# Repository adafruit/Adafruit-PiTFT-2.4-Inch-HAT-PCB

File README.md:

## Adafruit PiTFT 2.4 Inch HAT PCB

<a href="http://www.adafruit.com/products/2455"><br/>
Click here to purchase one from the Adafruit shop</a>

PCB files for the Adafruit PiTFT 2.4 Inch HAT. Format is EagleCAD schematic and board layout
* https://www.adafruit.com/product/2455

### DESCRIPTION
Is this not the cutest little display for the Raspberry Pi? It features a 2.4" display with 320x240 16-bit color pixels and a resistive touch overlay. The HAT uses the high speed SPI interface on the Pi and can use the mini display as a console, X window port, displaying images or video etc. Best of all it plugs right in on top!

It's designed to fit nicely onto the Pi Model Zero, A+, B+, Pi 2, Pi 3 - any Pi with a 2x20 connector.

This design uses the hardware SPI pins (SCK, MOSI, MISO, CE0, CE1) as well as GPIO #25 and #24. All other GPIO are unused. Since we had a tiny bit of space, there's 5 spots for optional slim tactile switches wired to five GPIOs, that you can use if you want to make a basic user interface. For example, you can use one as a power on/off button.

We have a right-angle 26-pin connector off to the side. You can connect a classic 26-pin Raspberry Pi GPIO cable in order to access the rest of the GPIO through a Cobbler, etc.

To make it super easy for use: we've created a custom kernel package based of off Notro's awesome framebuffer work, so you can install it over your existing Raspbian (or derivative) images in just a few commands.

Each order ships with an assembled HAT with 2.4" TFT display with resistive touchscreen and a 2x20 female socket header. Some light soldering is required to attach the header but it is easy work for anyone with a soldering iron & solder.Alternatively, you can use a stacking type header instead if you'd like to plug a 2x20 GPIO cable on top

Raspberry Pi, Pi enclosure, 26-pin GPIO cable, tactile switches are not included!

### License

Adafruit invests time and resources providing this open source design, please support Adafruit and open-source hardware by purchasing products from [Adafruit.com](https://www.adafruit.com)!

Creative Commons Attribution, Share-Alike license, check license.txt for more information All text above must be included in any redistribution - 
See license.txt for more information.

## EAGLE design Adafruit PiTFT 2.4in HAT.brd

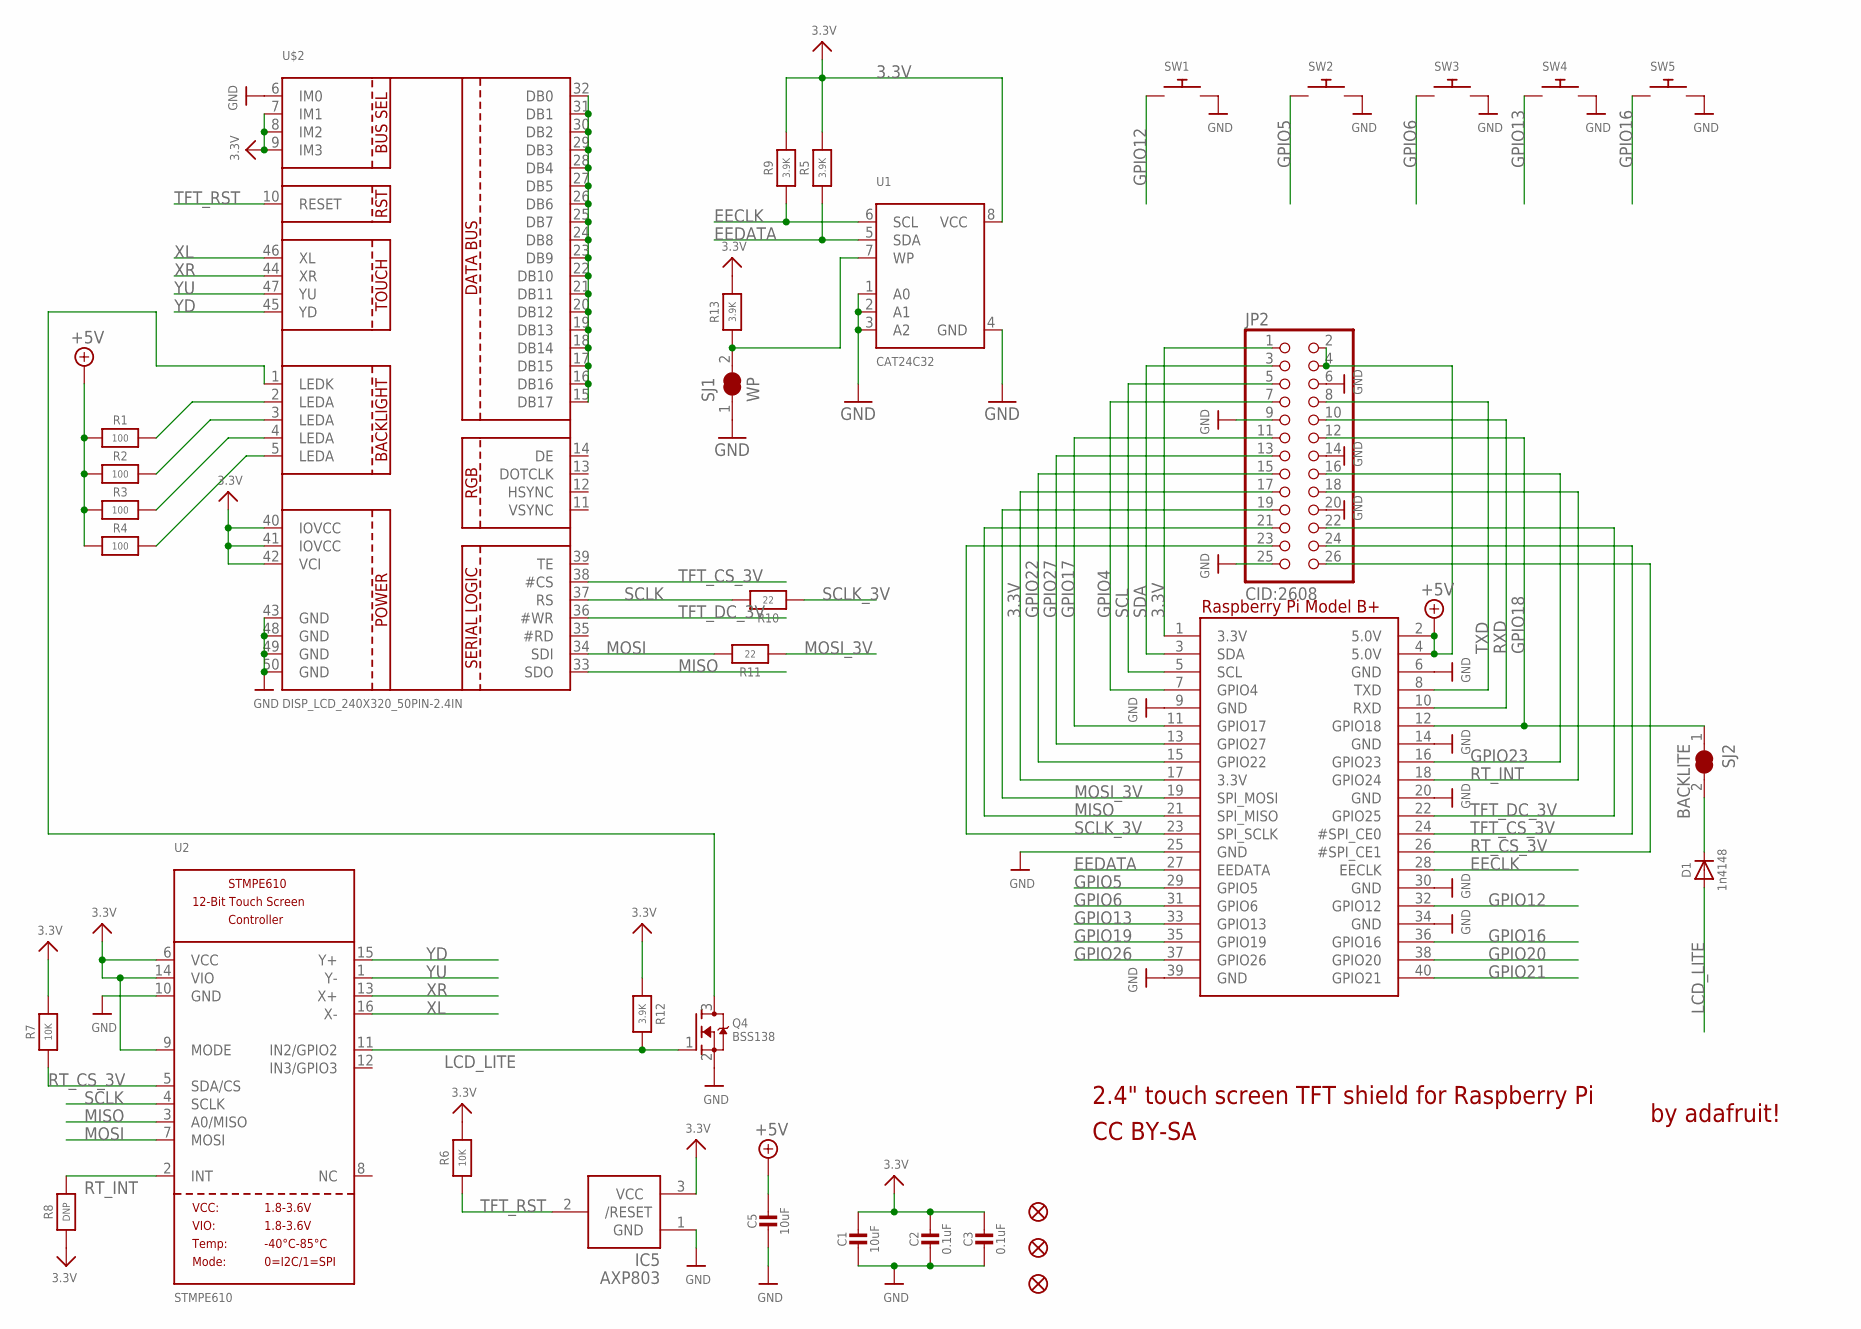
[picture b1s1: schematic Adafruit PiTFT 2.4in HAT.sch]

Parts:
C1, C5: 10uF; 0805-NO
C2, C3: 0.1uF; 0805-NO
D1: 1n4148; SOD-323
IC5: AXP803; SOT23
JP2: CID:2608; 2X13_SMT_MALE
Q4: BSS138; SOT23-WIDE
R1, R2, R3, R4: 100; 0805-NO
R5, R9, R12, R13: 3.9K; 0805-NO
R6, R7: 10K; 0805-NO
R8: DNP; 0805-NO
R10, R11: 22; 0805-NO
RPI1: RASPBERRYPI_BPLUS_HATNOSLOTS; PI_HAT_NOSLOTS
SJ1: WP; SOLDERJUMPER_CLOSEDWIRE
SJ2: BACKLITE; SOLDERJUMPER_CLOSEDWIRE
SW1, SW2, SW3, SW4, SW5: SWITCH_PUSHBUTTONEVQ-PE; TACT_PANA-EVQ
U1: CAT24C32; SOIC8_150MIL
U2: STMPE610; QFN16_3MM
U$2: DISP_LCD_240X320_50PIN-2.4IN; TFT_2.4IN_240X320_50PIN
U$10, U$11, U$18: FIDUCIAL""; FIDUCIAL_1MM

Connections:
3.3V: C1.1, C2.1, C3.1, IC5.3 (VCC), JP2.1, JP2.17, R5.2, R6.2, R7.2, R8.1, R9.2, R12.1, R13.2, RPI1.1 (3.3V), RPI1.17 (3.3V), U1.8 (VCC), U2.6 (VCC), U2.9 (MODE), U2.14 (VIO), U$2.7 (IM1), U$2.8 (IM2), U$2.9 (IM3), U$2.40 (IOVCC), U$2.41 (IOVCC), U$2.42 (VCI)
+5V: C5.1, JP2.2, JP2.4, R1.1, R2.1, R3.1, R4.1, RPI1.2 (5.0V), RPI1.4 (5.0V)
EECLK: R9.1, RPI1.28 (EECLK), U1.6 (SCL)
EEDATA: R5.1, RPI1.27 (EEDATA), U1.5 (SDA)
GND: C1.2, C2.2, C3.2, C5.2, IC5.1 (GND), JP2.6, JP2.9, JP2.14, JP2.20, JP2.25, Q4.2 (S), RPI1.6 (GND), RPI1.9 (GND), RPI1.14 (GND), RPI1.20 (GND), RPI1.25 (GND), RPI1.30 (GND), RPI1.34 (GND), RPI1.39 (GND), SJ1.1, SW1.P$2, SW2.P$2, SW3.P$2, SW4.P$2, SW5.P$2, U1.1 (A0), U1.2 (A1), U1.3 (A2), U1.4 (GND), U2.10 (GND), U$2.6 (IM0), U$2.43 (GND), U$2.48 (GND), U$2.49 (GND), U$2.50 (GND)
GPIO4: JP2.7, RPI1.7 (GPIO4)
GPIO5: RPI1.29 (GPIO5), SW2.P$1
GPIO6: RPI1.31 (GPIO6), SW3.P$1
GPIO12: RPI1.32 (GPIO12), SW1.P$1
GPIO13: RPI1.33 (GPIO13), SW4.P$1
GPIO16: RPI1.36 (GPIO16), SW5.P$1
GPIO17: JP2.11, RPI1.11 (GPIO17)
GPIO18: JP2.12, RPI1.12 (GPIO18), SJ2.1
GPIO19: RPI1.35 (GPIO19)
GPIO20: RPI1.38 (GPIO20)
GPIO21: RPI1.40 (GPIO21)
GPIO22: JP2.15, RPI1.15 (GPIO22)
GPIO23: JP2.16, RPI1.16 (GPIO23)
GPIO26: RPI1.37 (GPIO26)
GPIO27: JP2.13, RPI1.13 (GPIO27)
LCD_LITE: D1.A, Q4.1 (G), R12.2, U2.11 (IN2/GPIO2)
MISO: JP2.21, RPI1.21 (SPI_MISO), U2.3 (A0/MISO), U$2.33 (SDO)
MOSI: R11.2, U2.7 (MOSI), U$2.34 (SDI)
MOSI_3V: JP2.19, R11.1, RPI1.19 (SPI_MOSI)
unnamed: R1.2, U$2.2 (LEDA)
unnamed: R2.2, U$2.3 (LEDA)
unnamed: R3.2, U$2.4 (LEDA)
unnamed: Q4.3 (D), U$2.1 (LEDK)
unnamed: D1.C, SJ2.2
unnamed: U$2.15 (DB17), U$2.16 (DB16), U$2.17 (DB15), U$2.18 (DB14), U$2.19 (DB13), U$2.20 (DB12), U$2.21 (DB11), U$2.22 (DB10), U$2.23 (DB9), U$2.24 (DB8), U$2.25 (DB7), U$2.26 (DB6), U$2.27 (DB5), U$2.28 (DB4), U$2.29 (DB3), U$2.30 (DB2), U$2.31 (DB1), U$2.32 (DB0)
unnamed: R4.2, U$2.5 (LEDA)
unnamed: R13.1, SJ1.2, U1.7 (WP)
RT_CS_3V: JP2.26, R7.1, RPI1.26 (#SPI_CE1), U2.5 (SDA/CS)
RT_INT: JP2.18, R8.2, RPI1.18 (GPIO24), U2.2 (INT)
RXD: JP2.10, RPI1.10 (RXD)
SCL: JP2.5, RPI1.5 (SCL)
SCLK: R10.2, U2.4 (SCLK), U$2.37 (RS)
SCLK_3V: JP2.23, R10.1, RPI1.23 (SPI_SCLK)
SDA: JP2.3, RPI1.3 (SDA)
TFT_CS_3V: JP2.24, RPI1.24 (#SPI_CE0), U$2.38 (#CS)
TFT_DC_3V: JP2.22, RPI1.22 (GPIO25), U$2.36 (#WR)
TFT_RST: IC5.2 (/RESET), R6.1, U$2.10 (RESET)
TXD: JP2.8, RPI1.8 (TXD)
XL: U2.16 (X-), U$2.46 (XL)
XR: U2.13 (X+), U$2.44 (XR)
YD: U2.15 (Y+), U$2.45 (YD)
YU: U2.1 (Y-), U$2.47 (YU)

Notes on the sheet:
2.4" touch screen TFT shield for Raspberry Pi
by adafruit!
CC BY-SA

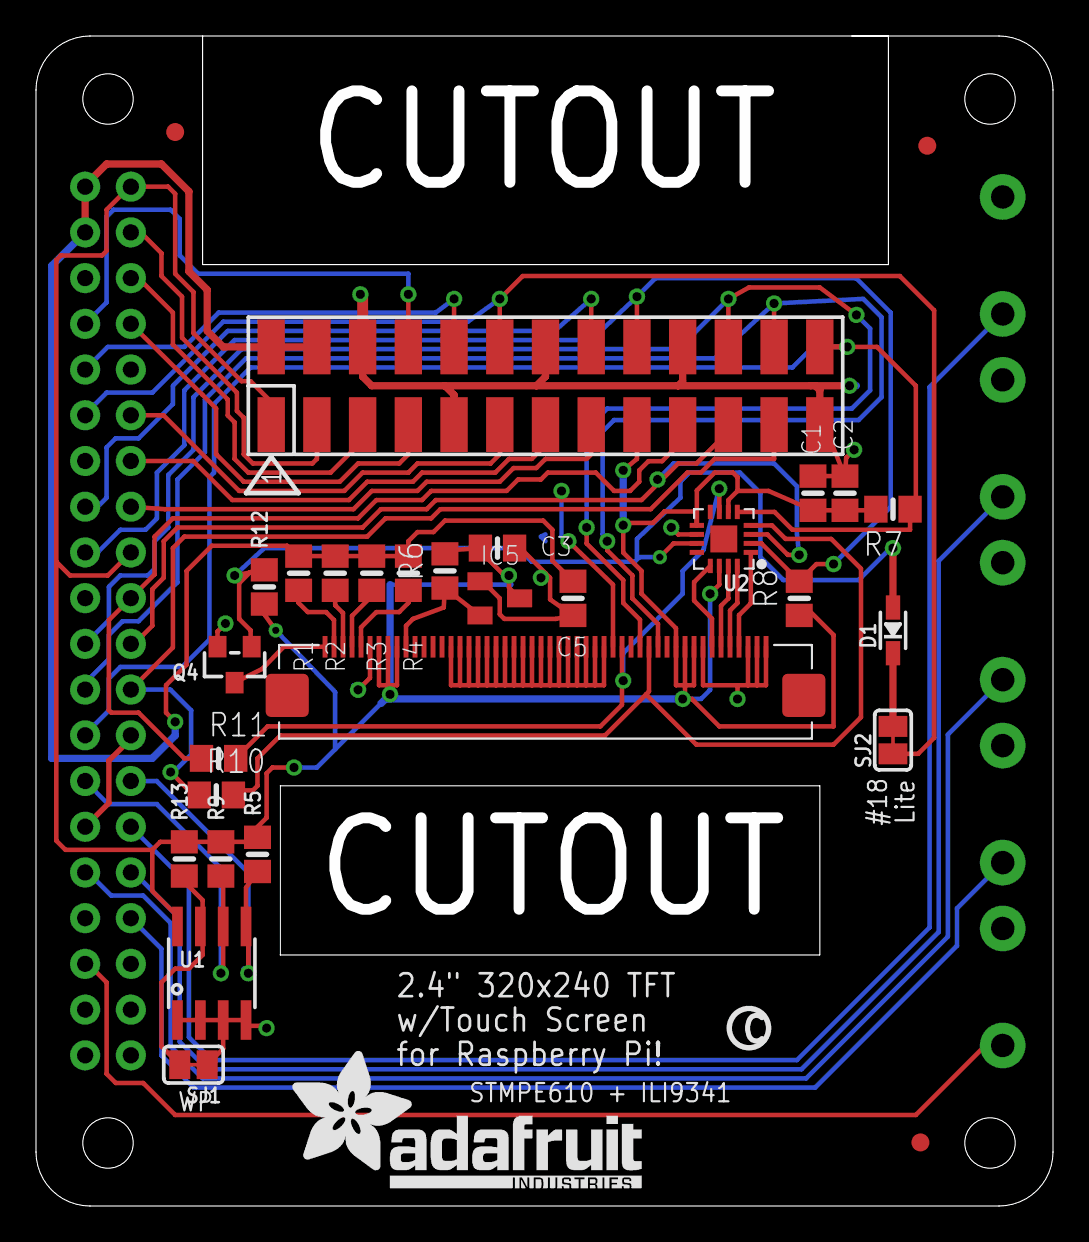
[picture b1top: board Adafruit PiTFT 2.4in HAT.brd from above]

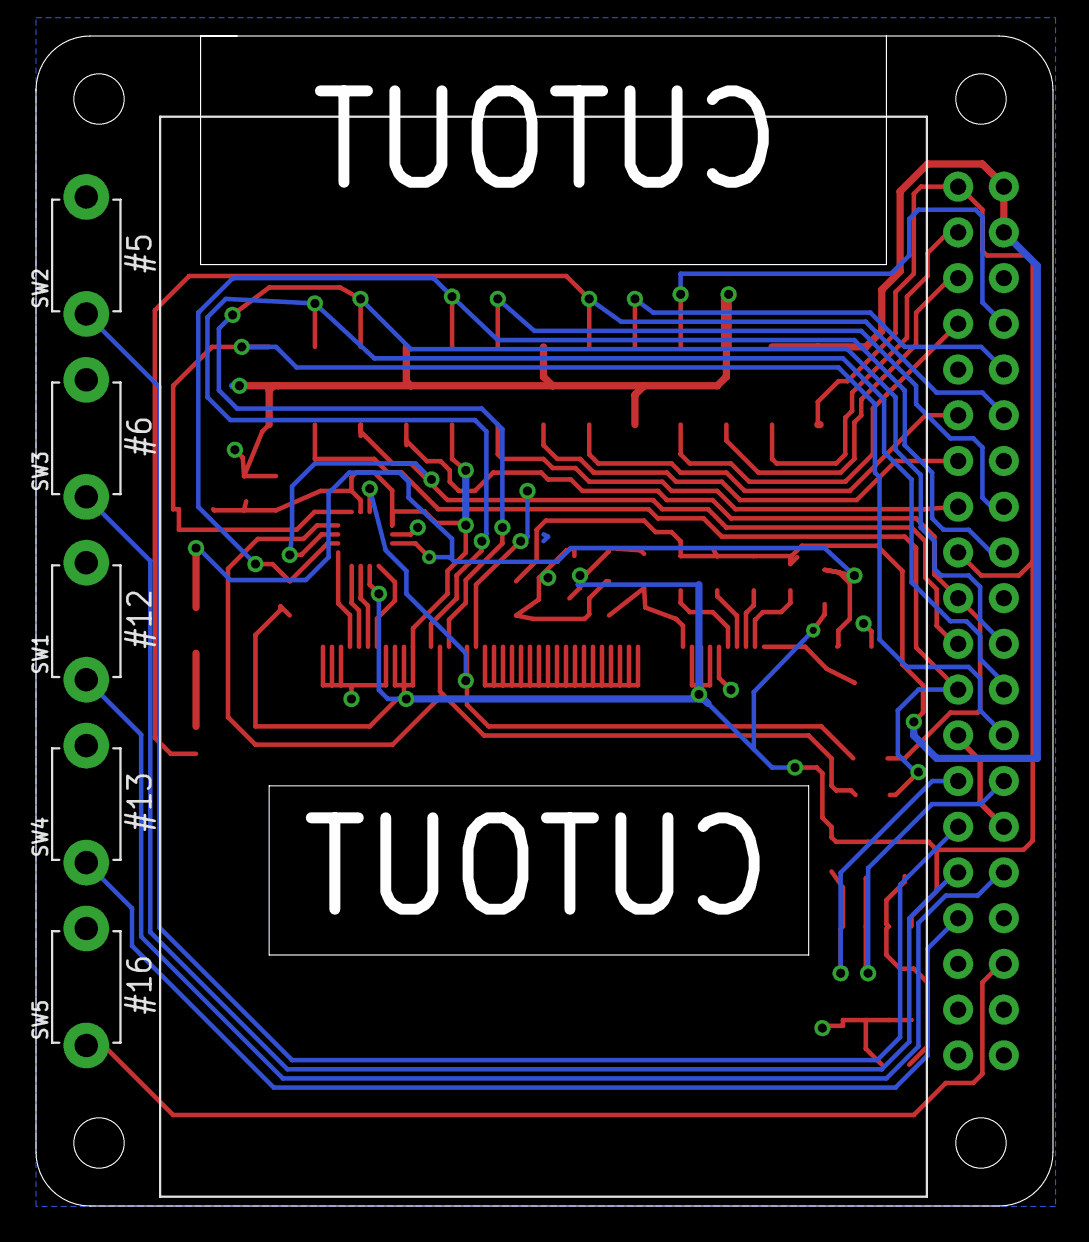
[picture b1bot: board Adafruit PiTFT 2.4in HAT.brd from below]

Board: 2 copper layers, 56.5 x 65.0 mm, 37 parts (7 on the bottom side), 43 nets.

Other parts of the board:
U$9: PCBFEAT-REV-056
U$23: ADAFRUIT_TEXT_20MM

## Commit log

2016-10-01 init
